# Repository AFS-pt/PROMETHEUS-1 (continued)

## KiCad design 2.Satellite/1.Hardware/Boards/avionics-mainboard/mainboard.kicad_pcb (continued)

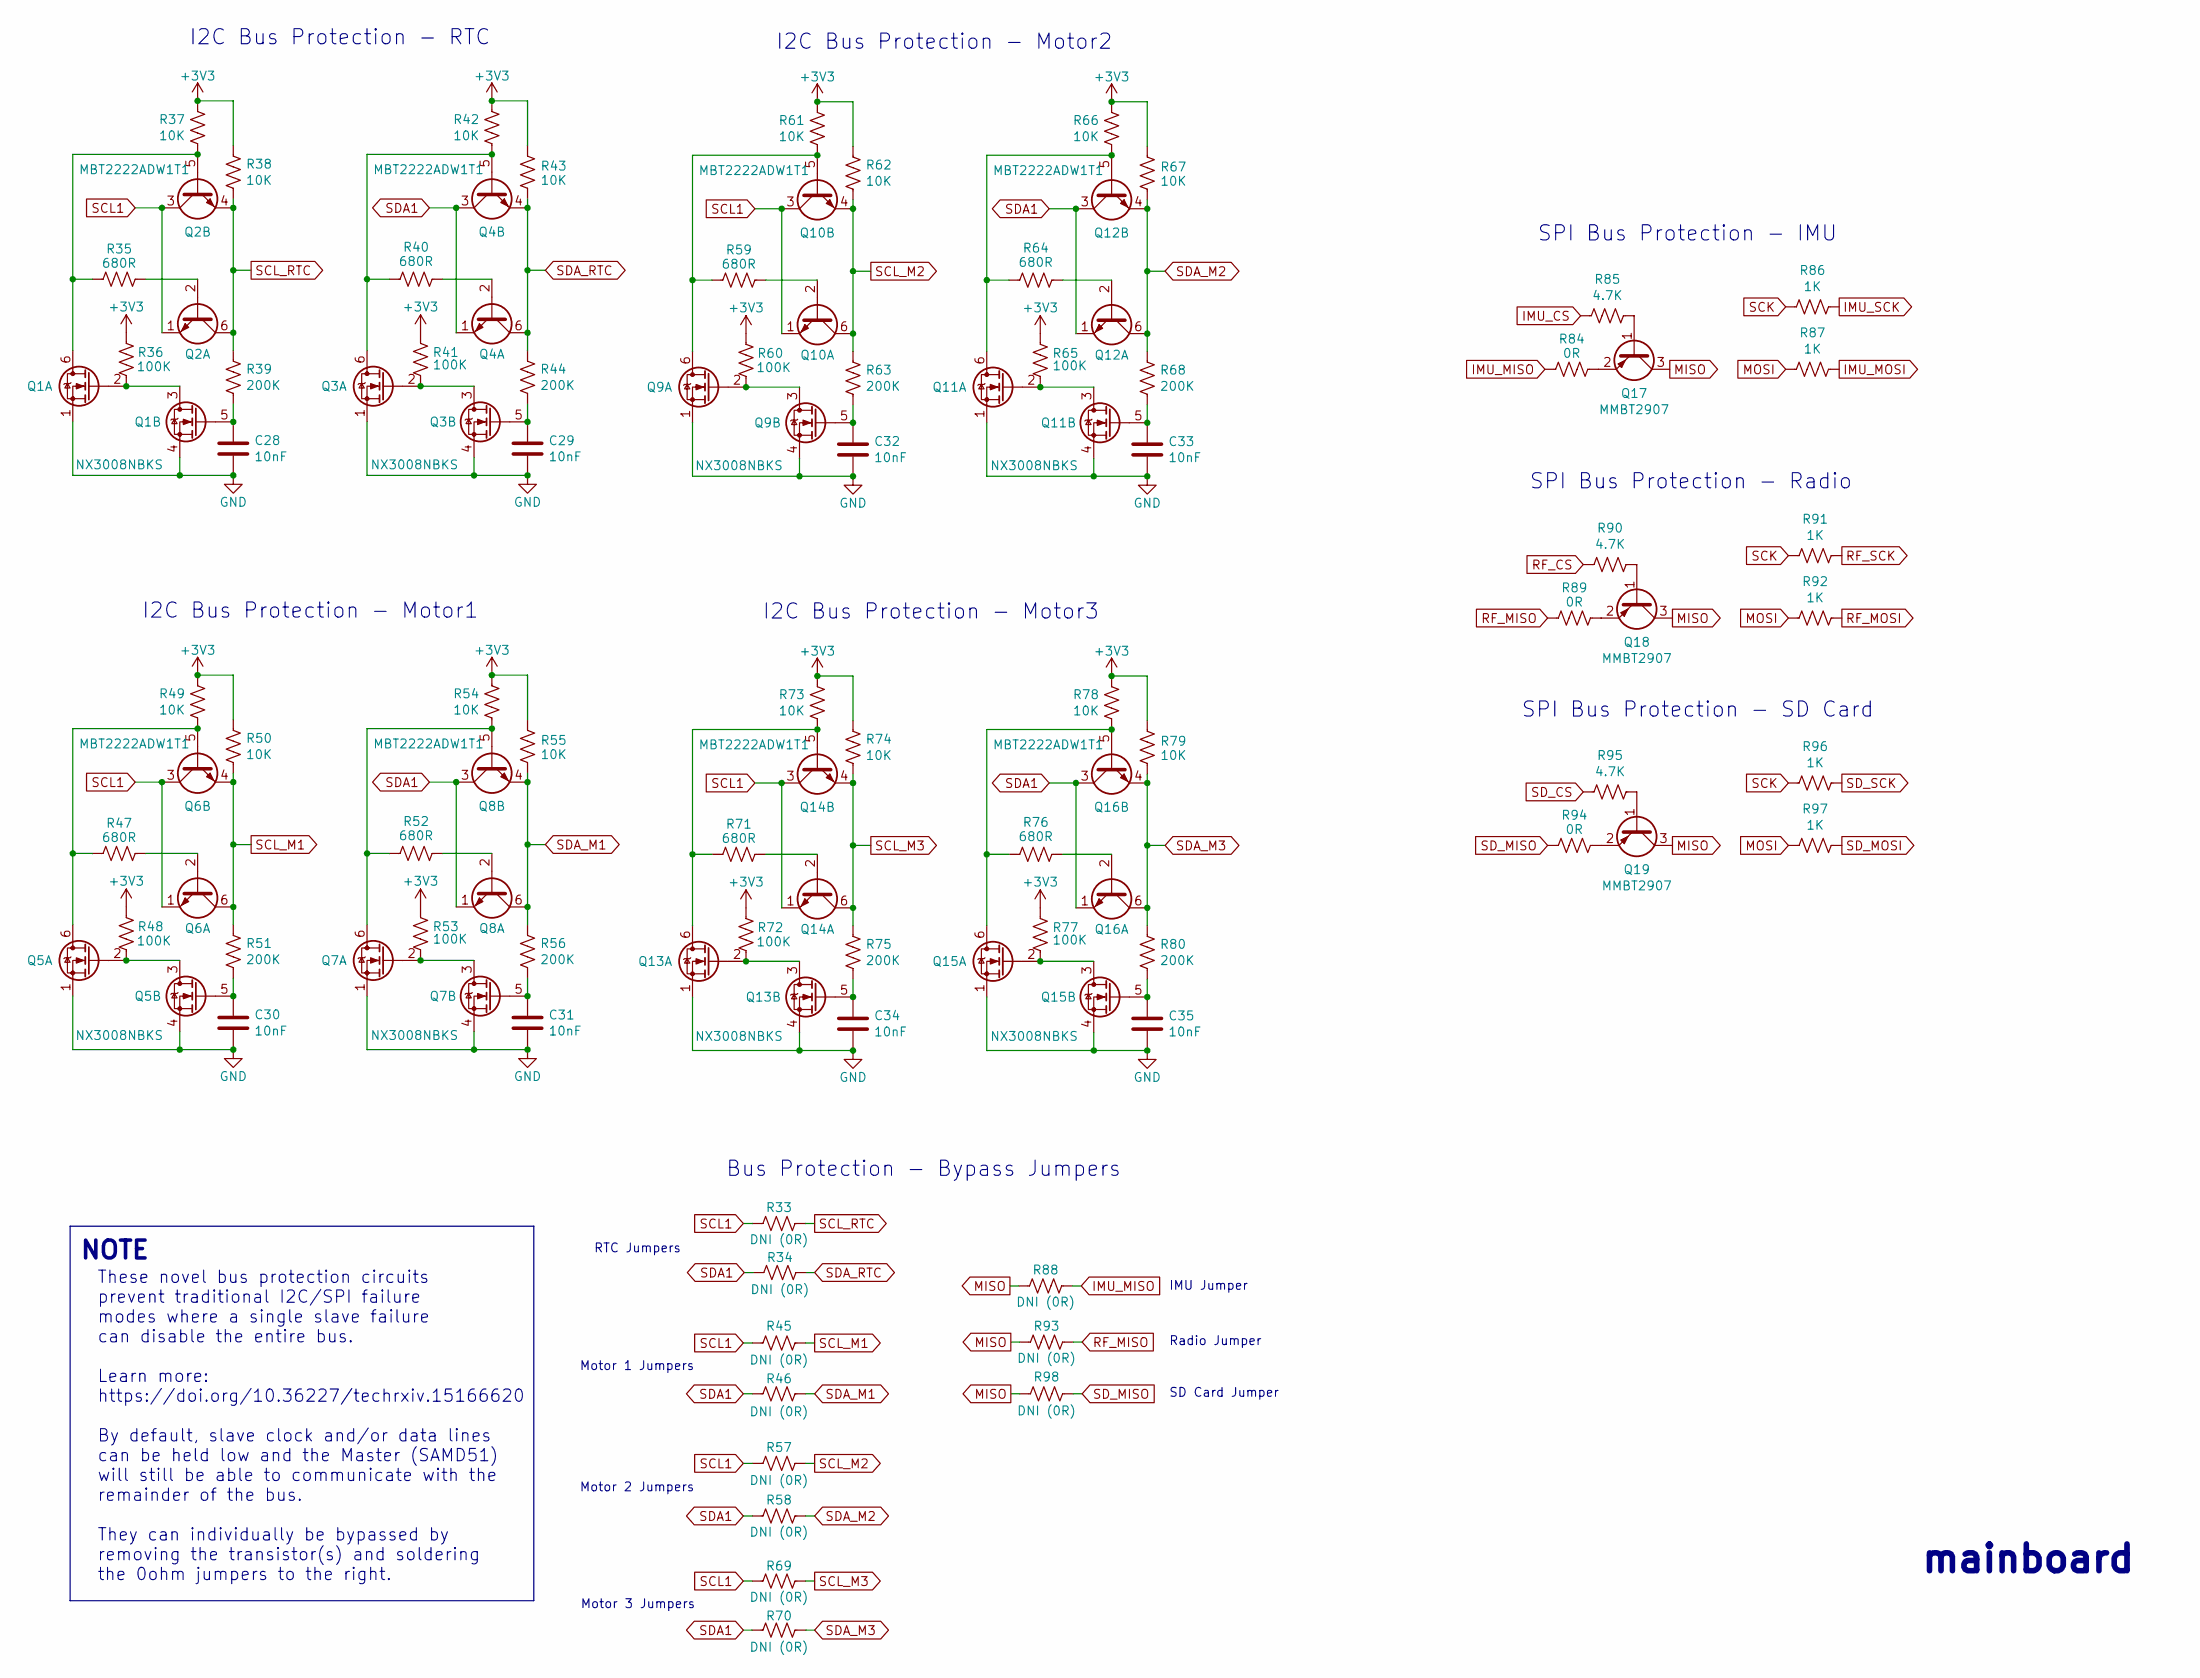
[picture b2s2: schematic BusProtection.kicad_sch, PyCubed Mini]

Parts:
C28, C29, C30, C31, C32, C33, C34, C35: 10nF; C_0603_1608Metric
Q1, Q3, Q5, Q7, Q9, Q11, Q13, Q15: NX3008NBKS; SOT-363_SC-70-6; Manufacturer_Part_Number NX3008NBKS
Q2, Q4, Q6, Q8, Q10, Q12, Q14, Q16: MBT2222ADW1T1; SOT-363_SC-70-6; Manufacturer_Part_Number MBT2222ADW1T1G
Q17, Q18, Q19: MMBT2907; SOT-23; Manufacturer_Part_Number MMBT2907ALT1G
R33, R34, R45, R46, R57, R58, R69, R70, R88, R93, R98: DNI (0R); R_0603_1608Metric
R35, R40, R47, R52, R59, R64, R71, R76: 680R; R_0603_1608Metric
R36, R41, R48, R53, R60, R65, R72, R77: 100K; R_0603_1608Metric
R37, R38, R42, R43, R49, R50, R54, R55, R61, R62, R66, R67, R73, R74, R78, R79: 10K; R_0603_1608Metric
R39, R44, R51, R56, R63, R68, R75, R80: 200K; R_0603_1608Metric
R84, R89, R94: 0R; R_0603_1608Metric
R85, R90, R95: 4.7K; R_0603_1608Metric
R86, R87, R91, R92, R96, R97: 1K; R_0603_1608Metric

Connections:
+3V3: R36.1, R37.1, R38.1, R41.1, R42.1, R43.1, R48.1, R49.1, R50.1, R53.1, R54.1, R55.1, R60.1, R61.1, R62.1, R65.1, R66.1, R67.1, R72.1, R73.1, R74.1, R77.1, R78.1, R79.1; also elsewhere on the board
GND: C28.2, C29.2, C30.2, C31.2, C32.2, C33.2, C34.2, C35.2, Q1.1 (S2), Q1.4 (S1), Q3.1 (S2), Q3.4 (S1), Q5.1 (S2), Q5.4 (S1), Q7.1 (S2), Q7.4 (S1), Q9.1 (S2), Q9.4 (S1), Q11.1 (S2), Q11.4 (S1), Q13.1 (S2), Q13.4 (S1), Q15.1 (S2), Q15.4 (S1); also elsewhere on the board
IMU_CS: R85.2; also elsewhere on the board
IMU_MISO: R84.2, R88.1; also elsewhere on the board
IMU_MOSI: R87.1; also elsewhere on the board
IMU_SCK: R86.1; also elsewhere on the board
MISO: Q17.3 (C), Q18.3 (C), Q19.3 (C), R88.2, R93.2, R98.2; also elsewhere on the board
MOSI: R87.2, R92.2, R97.2; also elsewhere on the board
unnamed: Q1.6 (D1), Q2.5 (B2), R35.2, R37.2
unnamed: Q1.2 (G2), Q1.3 (D2), R36.2
unnamed: C28.1, Q1.5 (G1), R39.2
unnamed: Q2.2 (B1), R35.1
unnamed: Q3.6 (D1), Q4.5 (B2), R40.2, R42.2
unnamed: Q3.2 (G2), Q3.3 (D2), R41.2
unnamed: C29.1, Q3.5 (G1), R44.2
unnamed: Q4.2 (B1), R40.1
unnamed: Q5.6 (D1), Q6.5 (B2), R47.2, R49.2
unnamed: Q5.2 (G2), Q5.3 (D2), R48.2
unnamed: C30.1, Q5.5 (G1), R51.2
unnamed: Q6.2 (B1), R47.1
unnamed: Q7.6 (D1), Q8.5 (B2), R52.2, R54.2
unnamed: Q7.2 (G2), Q7.3 (D2), R53.2
unnamed: C31.1, Q7.5 (G1), R56.2
unnamed: Q8.2 (B1), R52.1
unnamed: Q9.2 (G2), Q9.3 (D2), R60.2
unnamed: C32.1, Q9.5 (G1), R63.2
unnamed: Q10.2 (B1), R59.1
unnamed: Q9.6 (D1), Q10.5 (B2), R59.2, R61.2
unnamed: Q11.6 (D1), Q12.5 (B2), R64.2, R66.2
unnamed: Q11.2 (G2), Q11.3 (D2), R65.2
unnamed: C33.1, Q11.5 (G1), R68.2
unnamed: Q12.2 (B1), R64.1
unnamed: Q13.6 (D1), Q14.5 (B2), R71.2, R73.2
unnamed: Q13.2 (G2), Q13.3 (D2), R72.2
unnamed: C34.1, Q13.5 (G1), R75.2
unnamed: Q14.2 (B1), R71.1
unnamed: Q15.6 (D1), Q16.5 (B2), R76.2, R78.2
unnamed: Q15.2 (G2), Q15.3 (D2), R77.2
unnamed: C35.1, Q15.5 (G1), R80.2
unnamed: Q16.2 (B1), R76.1
unnamed: Q17.1 (B), R85.1
unnamed: Q17.2 (E), R84.1
unnamed: Q18.1 (B), R90.1
unnamed: Q18.2 (E), R89.1
unnamed: Q19.1 (B), R95.1
unnamed: Q19.2 (E), R94.1
RF_CS: R90.2; also elsewhere on the board
RF_MISO: R89.2, R93.1; also elsewhere on the board
RF_MOSI: R92.1; also elsewhere on the board
RF_SCK: R91.1; also elsewhere on the board
SCK: R86.2, R91.2, R96.2; also elsewhere on the board
SCL1: Q2.1 (E1), Q2.3 (C2), Q6.1 (E1), Q6.3 (C2), Q10.1 (E1), Q10.3 (C2), Q14.1 (E1), Q14.3 (C2), R33.2, R45.2, R57.2, R69.2; also elsewhere on the board
SCL_M1: Q6.4 (E2), Q6.6 (C1), R45.1, R50.2, R51.1; also elsewhere on the board
SCL_M2: Q10.4 (E2), Q10.6 (C1), R57.1, R62.2, R63.1; also elsewhere on the board
SCL_M3: Q14.4 (E2), Q14.6 (C1), R69.1, R74.2, R75.1; also elsewhere on the board
SCL_RTC: Q2.4 (E2), Q2.6 (C1), R33.1, R38.2, R39.1; also elsewhere on the board
SDA1: Q4.1 (E1), Q4.3 (C2), Q8.1 (E1), Q8.3 (C2), Q12.1 (E1), Q12.3 (C2), Q16.1 (E1), Q16.3 (C2), R34.2, R46.2, R58.2, R70.2; also elsewhere on the board
SDA_M1: Q8.4 (E2), Q8.6 (C1), R46.1, R55.2, R56.1; also elsewhere on the board
SDA_M2: Q12.4 (E2), Q12.6 (C1), R58.1, R67.2, R68.1; also elsewhere on the board
SDA_M3: Q16.4 (E2), Q16.6 (C1), R70.1, R79.2, R80.1; also elsewhere on the board
SDA_RTC: Q4.4 (E2), Q4.6 (C1), R34.1, R43.2, R44.1; also elsewhere on the board
SD_CS: R95.2; also elsewhere on the board
SD_MISO: R94.2, R98.1; also elsewhere on the board
SD_MOSI: R97.1; also elsewhere on the board
SD_SCK: R96.1; also elsewhere on the board

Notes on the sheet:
SPI Bus Protection - IMU
Motor 3 Jumpers
I2C Bus Protection - RTC
I2C Bus Protection - Motor3
I2C Bus Protection - Motor2
Motor 1 Jumpers
NOTE
SPI Bus Protection - SD Card
Bus Protection - Bypass Jumpers
I2C Bus Protection - Motor1
RTC Jumpers
IMU Jumper
Radio Jumper
mainboard
SPI Bus Protection - Radio
SD Card Jumper
Motor 2 Jumpers
These novel bus protection circuits prevent traditional I2C/SPI failure modes where a single slave failure can disable the entire bus. Learn more: https://doi.org/10.36227/techrxiv.15166620 By default, slave clock and/or data lines can be held low and the Master (SAMD51) will still be able to commu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

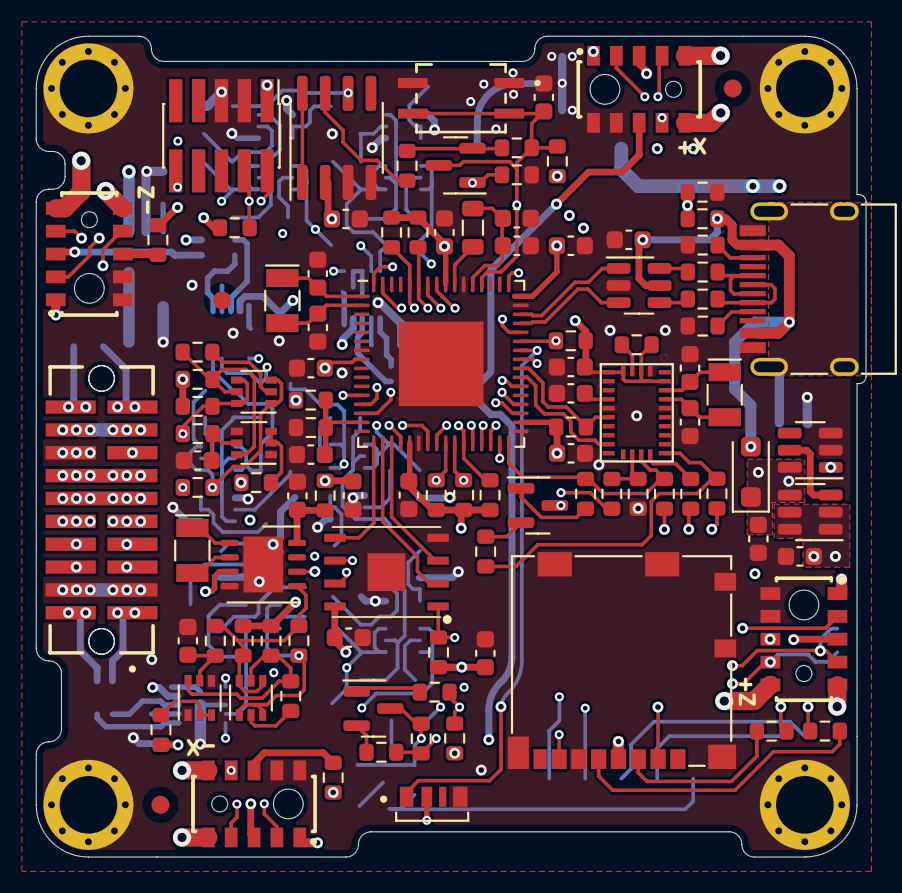
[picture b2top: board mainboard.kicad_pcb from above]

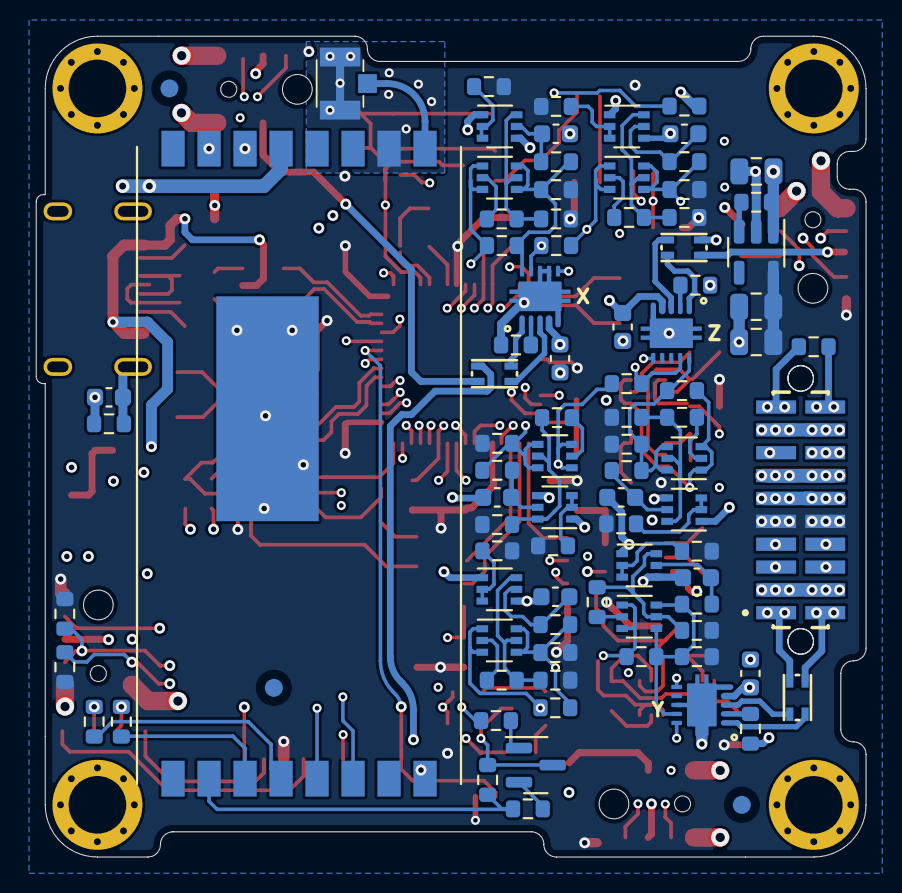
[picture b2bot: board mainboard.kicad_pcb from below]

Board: 4 copper layers, 46.1 x 45.6 mm, 196 parts (86 on the bottom side), 145 nets.

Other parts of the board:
Ref**: Val**; pycubed_mini_half

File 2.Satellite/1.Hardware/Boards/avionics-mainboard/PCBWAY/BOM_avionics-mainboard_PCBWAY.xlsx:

*Designator | *Qty | Manufacturer | *Mfg Part # | Description / Value | *Package/Footprint | Type | Your Instructions / Notes
C28-C35 | 8 | KYOCERA AVX | 06031C103K4T4A | CAP CER 10000PF 100V X7R 0603 | 0603
C26 | 1 | KYOCERA AVX | 06031C472K4T4A | CAP CER 4700PF 100V X7R 0603 | 0603
C1, C2, C3, C4, C5, C10, C13, C19, C21, C23, C24, C25, C27, C36 | 14 | KYOCERA AVX | 06035C104K4T2A | CAP CER 0.1UF 50V X7R 0603 | 0603
C37, C38 | 2 | KYOCERA AVX | 0603YA220J4T2A | CAP CER 22PF 16V C0G/NP0 0603 | 0603 | SMD
C6, C7 | 2 | TDK Corporation | CGA3E2NP01H040C080AA | CAP CER 4PF 50V NP0 0603 | 0603
C8, C17, C18 | 3 | Murata Electronics | GRT188R61C106KE13D | CAP CER 10UF 16V X5R 0603 | 0603
C9, C11, C12, C20, C22 | 5 | Murata Electronics | GRT188R61H105KE13D | CAP CER 1UF 50V X5R 0603 | 0603
C16 | 1 | TDK Corporation | CGA4J1X8R1E105K125AC | CAP CER 1UF 25V X8R 0805 | 0805
C14, C15 | 2 | Murata Electronics | GRT21BC71E106KE13L | CAP CER 10UF 25V X7S 0805 | 0805
J1 | 1 | Amphenol ICC (FCI) | 20021121-00010C4LF | CONN HEADER SMD 10POS 1.27MM |  | SMD
J4 | 1 | GCT | USB4105-GF-A | CONN RCP USB2.0 TYP C 24P SMD RA |  | SMD
Y3 | 1 | Micro Crystal | CC7V-T1A-32.768k-12.5pF-20PPM-TC-QA | Crystals 32.768 kHz 12.5 pF +/-20 PPM AEC-Q200 |  | SMD
Y1, Y2 | 2 | Micro Crystal | CC7V-T1A-32.768k-7pF-20PPM-TB-QA | Crystals 32.768 kHz 7.0 pF +/-20 PPM AEC-Q200 |  | SMD
D2 | 1 | Panjit International Inc. | MBR1020VL-AU_R1_000A1 | DIODE SCHOTTKY 20V 1A SOD123FL | SOD-123F
L1 | 1 | Coilcraft | 0805LS-103XGRC | RF INDUCTOR, FERRITE CORE, 2% TO | 0805
U12 | 1 | CEVA Technologies, Inc. | BNO085 | IMU ACCEL/GYRO/MAG I2C 32BIT | 28-LGA
J3 | 1 | Molex | 1040310811 | CONN MICRO SD CARD PUSH-PULL R/A |  | SMD
U4 | 1 | Everspin Technologies Inc. | MR25H40DF | IC RAM 4MBIT SPI 40MHZ 8DFN | 8-DFN-EP
U6 | 1 | HOPE MICROELECTRONICS | RFM98PW-433S2 | Module: transceiver; RF; FSK,GFSK,GMSK,LoRa,MSK,OOK; 433.92MHz |  | SMD
J7, J8, J9, J10 | 4 | Samtec Inc. | CLP-105-02-F-DH-A | CONN RCPT 10P 0.05 GOLD SMD R/A |  | SMD
J5 | 1 | Samtec Inc. | SFC-110-T2-F-D-A | CONN RCPT 20POS 0.05 GOLD SMD |  | SMD
J6 | 1 | Samtec Inc. | TFM-110-12-L-D-A | CONN HEADER SMD 20POS 1.27MM |  | SMD
D1 | 1 | Adafruit Industries LLC | 4691 | ADDRESS LED DISCRETE RGB 4X2MM |  | SMD
SW1 | 1 | Würth Elektronik | 434331045822 | SWITCH TACTILE SPST-NO 0.05A 12V |  | SMD
FL1, FL2, FL3 | 3 | Bourns Inc. | SRF2012A-670YA | CMC 400MA 2LN 67OHM SMD AEC-Q200 | 0805 | SMD
J2 | 1 | Hirose Electric Co Ltd | U.FL-R-SMT-1(80) | CONN U.FL RCPT STR 50 OHM SMD |  | SMD
U7-U9 | 3 | Texas Instruments | DRV8830DRCT | IC MTRDRV BIPLR 2.75-6.8V 10VSON | 10-VSON
U1 | 1 | Microchip Technology | ATSAMD51J19A-M | IC MCU 32BIT 512KB FLASH 64QFN | 64-QFN
U2 | 1 | Analog Devices Inc./Maxim Integrated | MAX706RESA+T | IC SUPERVISOR 1 CHANNEL 8SOIC | 8-SOIC
U11 | 1 | NXP USA Inc. | PCF8523TK/1,118 | IC RTC CLK/CALENDAR I2C 8HVSON | 8-HVSON
Q21 | 1 | Infineon Technologies | IRLML2803TRPBF | MOSFET N-CH 30V 1.2A SOT23 | SOT-23-3
Q17-Q19 | 3 | Diodes Incorporated | MMBT2907A-7-F | TRANS PNP 60V 0.6A SOT23-3 | SOT-23-3
U3 | 1 | Diodes Incorporated | AP2112K-3.3TRG1 | IC REG LINEAR 3.3V 600MA SOT25 | SOT-25
Q20 | 1 | Vishay Siliconix | SQ3495EV-T1_GE3 | MOSFET P-CH 30V 8A 6TSOP | SOT-23-6 | SMD
U10 | 1 | STMicroelectronics | USBLC6-2SC6 | TVS DIODE 5.25VWM 17VC SOT23-6 | SOT-23-6
Q2, Q4, Q6, Q8, Q10, Q12, Q14, Q16 | 8 | onsemi | MBT2222ADW1T1G | TRANS 2NPN 40V 0.6A SC88/SC70-6 | SOT-363
Q1, Q3, Q5, Q7, Q9, Q11, Q13, Q15 | 8 | Nexperia USA Inc. | NX3008NBKS,115 | MOSFET 2N-CH 30V 0.35A 6TSSOP | 6-TSSOP
U5 | 1 | Analog Devices Inc. | LTC4412ES6#TRMPBF | IC OR CTRLR SRC SELECT TSOT23-6 | TSOT-23-6
R39, R44, R51, R56, R63, R68, R75, R80, R100 | 9 | Stackpole Electronics Inc | RMCF0603FT200K | RES 200K OHM 1% 1/10W 0603 | 0603
R28, R29 | 2 | Stackpole Electronics Inc | RMCF0603FT22R0 | RES 22 OHM 1% 1/10W 0603 | 0603
R35, R40, R47, R52, R59, R64, R71, R76 | 8 | Stackpole Electronics Inc | RMCF0603FT680R | RES 680 OHM 1% 1/10W 0603 | 0603
R13, R20-R22, R26, R30-R32, R84, R89, R94 | 11 | Stackpole Electronics Inc | RMCF0603ZT0R00 | RES 0 OHM JUMPER 1/10W 0603 | 0603
R23 | 1 | Stackpole Electronics Inc | RNCF0603BKC1M00 | RES 1M OHM 0.1% 1/10W 0603 | 0603
R3-R10, R14, R16-R19, R37, R38, R42, R43, R49, R50, R54, R55, R61, R62, R66, R6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 | 32 | Stackpole Electronics Inc | RNCF0603BTE10K0 | RES 10K OHM 0.1% 1/6W 0603 | 0603
R1, R2, R11, R27, R36, R41, R48, R53, R60, R65, R72, R77 | 12 | Stackpole Electronics Inc | RNCF0603DTE100K | RES 100K OHM 0.5% 1/6W 0603 | 0603
R12, R15, R86, R87, R91, R92, R96, R97 | 8 | Stackpole Electronics Inc | RNCF0603DTE1K00 | RES 1K OHM 0.5% 1/6W 0603 | 0603
R85, R90, R95 | 3 | Stackpole Electronics Inc | RNCF0603DTE4K70 | RES 4.7K OHM 0.5% 1/6W 0603 | 0603
R24, R25 | 2 | Stackpole Electronics Inc | RNCF0603DTE5K10 | RES 5.1K OHM 0.5% 1/6W 0603 | 0603

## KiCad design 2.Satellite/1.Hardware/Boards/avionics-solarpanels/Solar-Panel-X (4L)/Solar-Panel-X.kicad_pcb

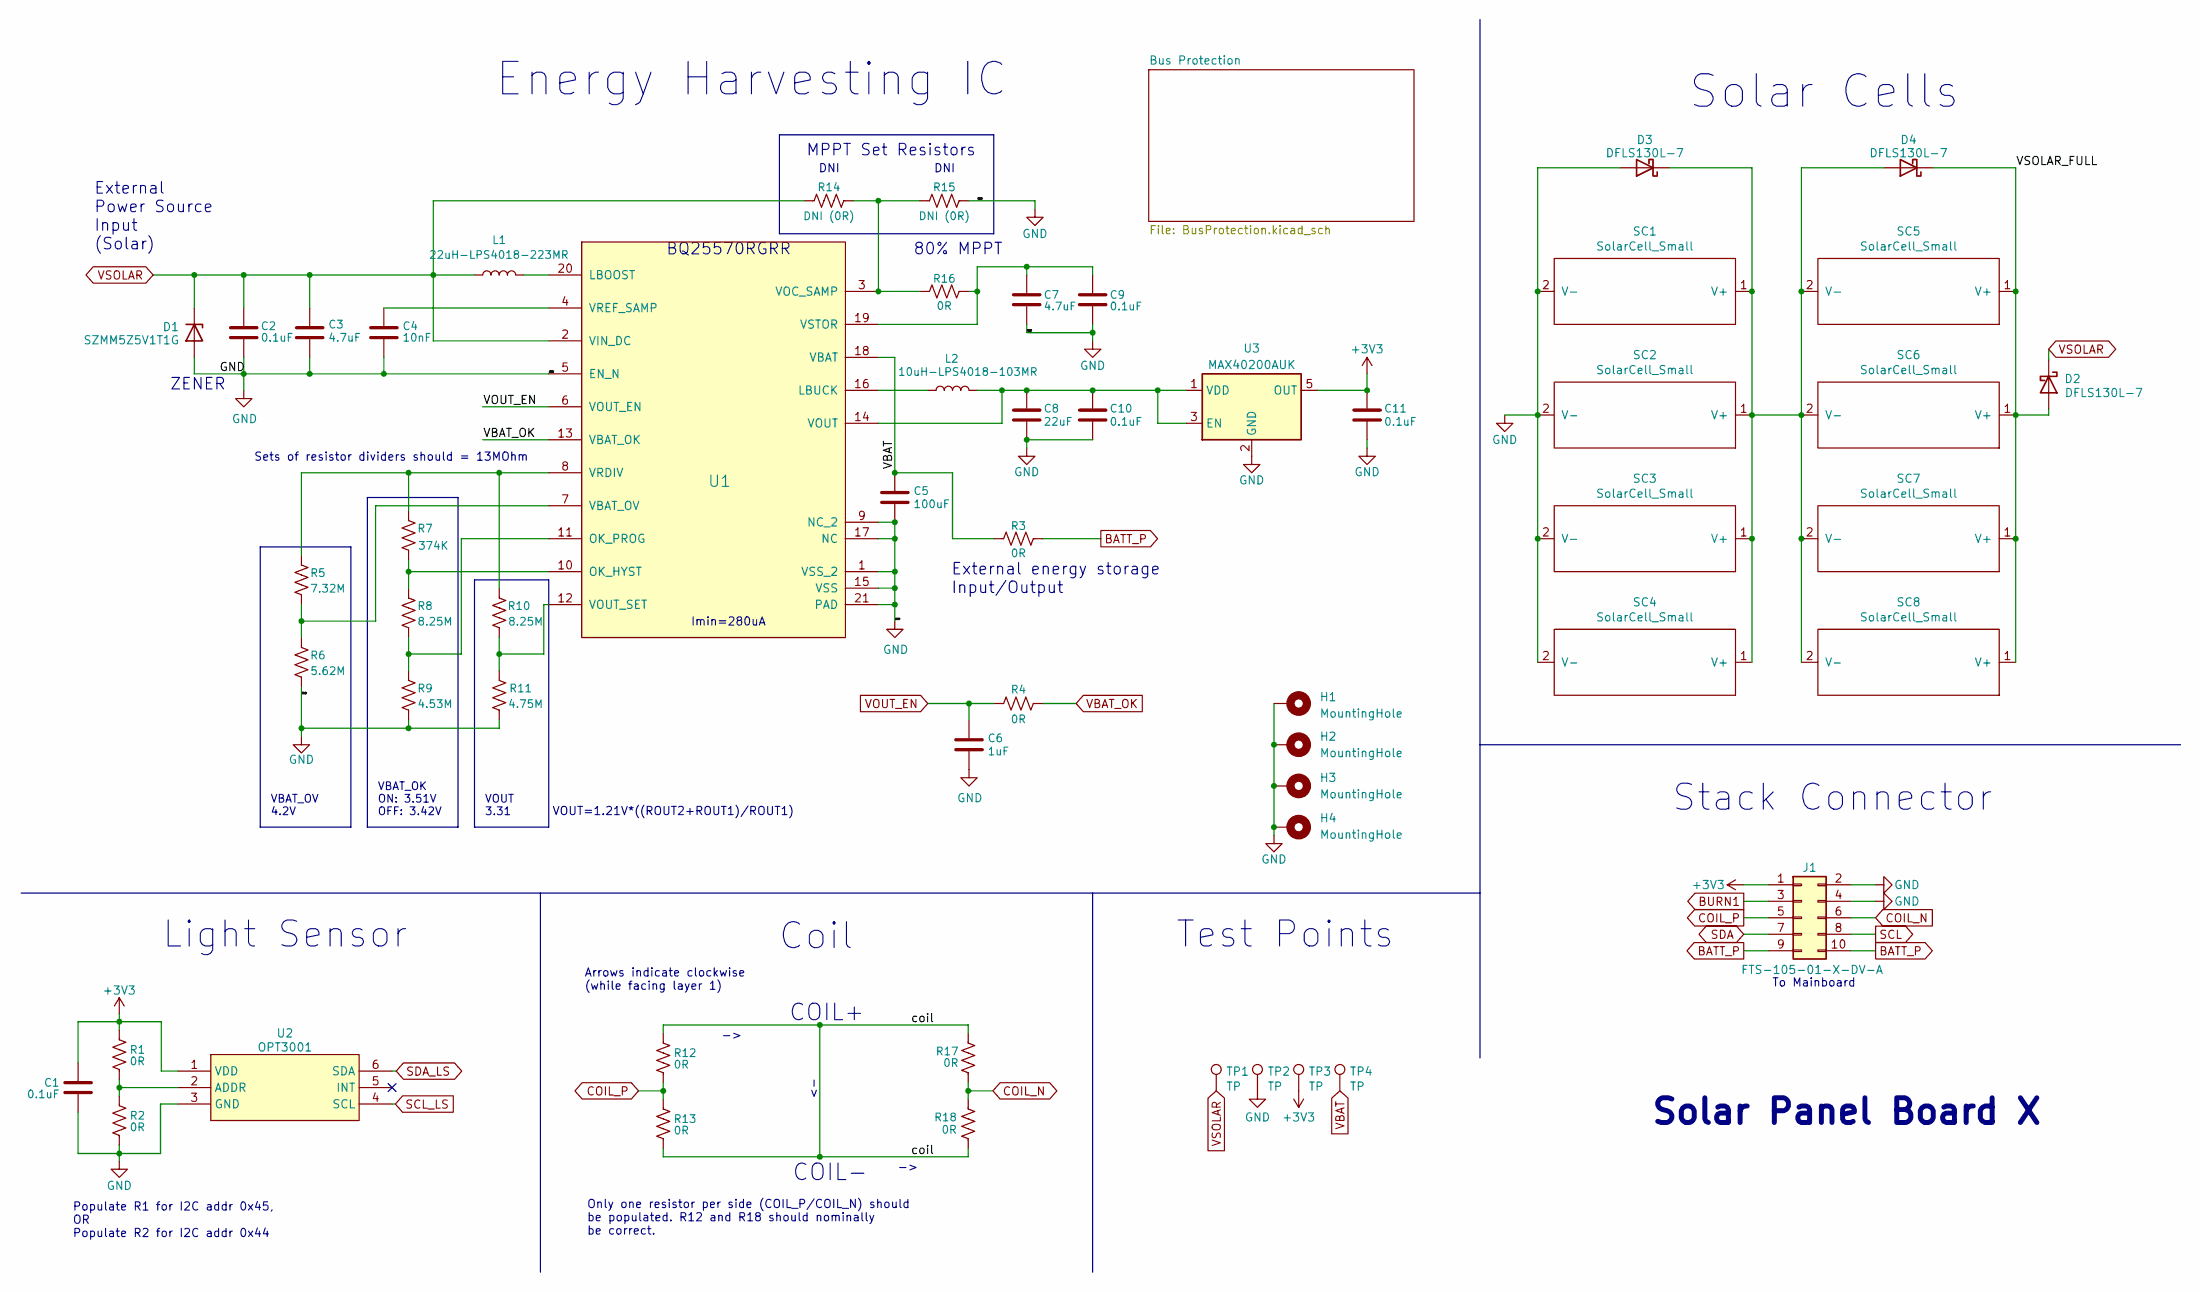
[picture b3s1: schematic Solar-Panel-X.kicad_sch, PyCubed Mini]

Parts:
C1: 0.1uF; C_0402_1005Metric
C2, C9, C10, C11: 0.1uF; C_0603_1608Metric
C3, C7: 4.7uF; C_0603_1608Metric
C4: 10nF; C_0603_1608Metric
C5: 100uF; C_0805_2012Metric
C6: 1uF; C_0603_1608Metric
C8: 22uF; C_0603_1608Metric
D1: SZMM5Z5V1T1G; D_SOD-523
D2, D3, D4: DFLS130L-7; D_PowerDI-123
H1, H2, H3, H4: MountingHole; MountingHole_2.2mm_M2_DIN965_Pad_TopBottom
J1: FTS-105-01-X-DV-A; SAMTEC-FTS-105-01-X-DV-A
L1: 22uH-LPS4018-223MR; LPS4018
L2: 10uH-LPS4018-103MR; LPS4018
R1, R2: 0R; R_0402_1005Metric
R3, R4, R12, R13, R16, R17, R18: 0R; R_0603_1608Metric
R5: 7.32M; R_0603_1608Metric
R6: 5.62M; R_0603_1608Metric
R7: 374K; R_0603_1608Metric
R8, R10: 8.25M; R_0603_1608Metric
R9: 4.53M; R_0603_1608Metric
R11: 4.75M; R_0603_1608Metric
R14, R15: DNI (0R); R_0603_1608Metric
SC1, SC2, SC3, SC4, SC5, SC6, SC7, SC8: SolarCell_Small; KXOB25-05X3F
TP1, TP2, TP3, TP4: TP; TestPoint_THTPad_D1.0mm_Drill0.5mm
U1: BQ25570RGRR; QFN50P350X350X100-21N-D
U2: OPT3001
U3: MAX40200AUK; SOT-23-5

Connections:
+3V3: C1.2, C11.1, J1.1, R1.2, TP3.1, U2.1 (VDD), U3.5 (OUT); also elsewhere on the board
/VSOLAR_FULL: D2.2 (A), D4.1 (K), SC5.1 (V+), SC6.1 (V+), SC7.1 (V+), SC8.1 (V+)
/coil: R12.2, R13.1, R17.2, R18.1
BATT_P: J1.9, J1.10, R3.1
BURN1: J1.3
COIL_N: J1.6, R17.1, R18.2
COIL_P: J1.5, R12.1, R13.2
GND: C1.1, C2.2, C3.2, C4.2, C5.2, C6.2, C7.2, C8.2, C9.2, C10.2, C11.2, D1.2 (A), D3.2 (A), H1.1, H2.1, H3.1, H4.1, J1.2, J1.4, R2.1, R6.1, R9.1, R11.1, R15.1, SC1.2 (V-), SC2.2 (V-), SC3.2 (V-), SC4.2 (V-), TP2.1, U1.1 (VSS_2), U1.5 (EN_N), U1.9 (NC_2), U1.15 (VSS), U1.17 (NC), U1.21 (PAD), U2.3 (GND), U2.7 (GND), U3.2 (GND); also elsewhere on the board
unnamed: D3.1 (K), D4.2 (A), SC1.1 (V+), SC2.1 (V+), SC3.1 (V+), SC4.1 (V+), SC5.2 (V-), SC6.2 (V-), SC7.2 (V-), SC8.2 (V-)
unnamed: L1.2, U1.20 (LBOOST)
unnamed: L2.1, U1.16 (LBUCK)
unnamed: R7.1, R8.2, U1.10 (OK_HYST)
unnamed: R8.1, R9.2, U1.11 (OK_PROG)
unnamed: R5.1, R6.2, U1.7 (VBAT_OV)
unnamed: R14.1, R15.2, R16.2, U1.3 (VOC_SAMP)
unnamed: C8.1, C10.1, L2.2, U1.14 (VOUT), U3.1 (VDD), U3.3 (EN)
unnamed: R10.1, R11.2, U1.12 (VOUT_SET)
unnamed: R5.2, R7.2, R10.2, U1.8 (VRDIV)
unnamed: C4.1, U1.4 (VREF_SAMP)
unnamed: C7.1, C9.1, R16.1, U1.19 (VSTOR)
unnamed: R1.1, R2.2, U2.2 (ADDR)
SCL: J1.8; also elsewhere on the board
SCL_LS: U2.4 (SCL); also elsewhere on the board
SDA: J1.7; also elsewhere on the board
SDA_LS: U2.6 (SDA); also elsewhere on the board
VBAT: C5.1, R3.2, TP4.1, U1.18 (VBAT)
VBAT_OK: R4.1, U1.13 (VBAT_OK)
VOUT_EN: C6.1, R4.2, U1.6 (VOUT_EN)
VSOLAR: C2.1, C3.1, D1.1 (K), D2.1 (K), L1.1, R14.2, TP1.1, U1.2 (VIN_DC)

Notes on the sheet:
80% MPPT
DNI
Populate R1 for I2C addr 0x45, OR Populate R2 for I2C addr 0x44
Solar Cells
External Power Source Input (Solar)
Only one resistor per side (COIL_P/COIL_N) should be populated. R12 and R18 should nominally be correct.
Stack Connector
VOUT 3.31
Energy Harvesting IC
MPPT Set Resistors
Arrows indicate clockwise (while facing layer 1)
Test Points
External energy storage Input/Output
COIL+
BQ25570RGRR
Light Sensor
Solar Panel Board X
VOUT=1.21V*((ROUT2+ROUT1)/ROUT1)
VBAT_OV 4.2V
VBAT_OK ON: 3.51V OFF: 3.42V
COIL-
Sets of resistor dividers should = 13MOhm
Imin=280uA
ZENER
To Mainboard
Coil

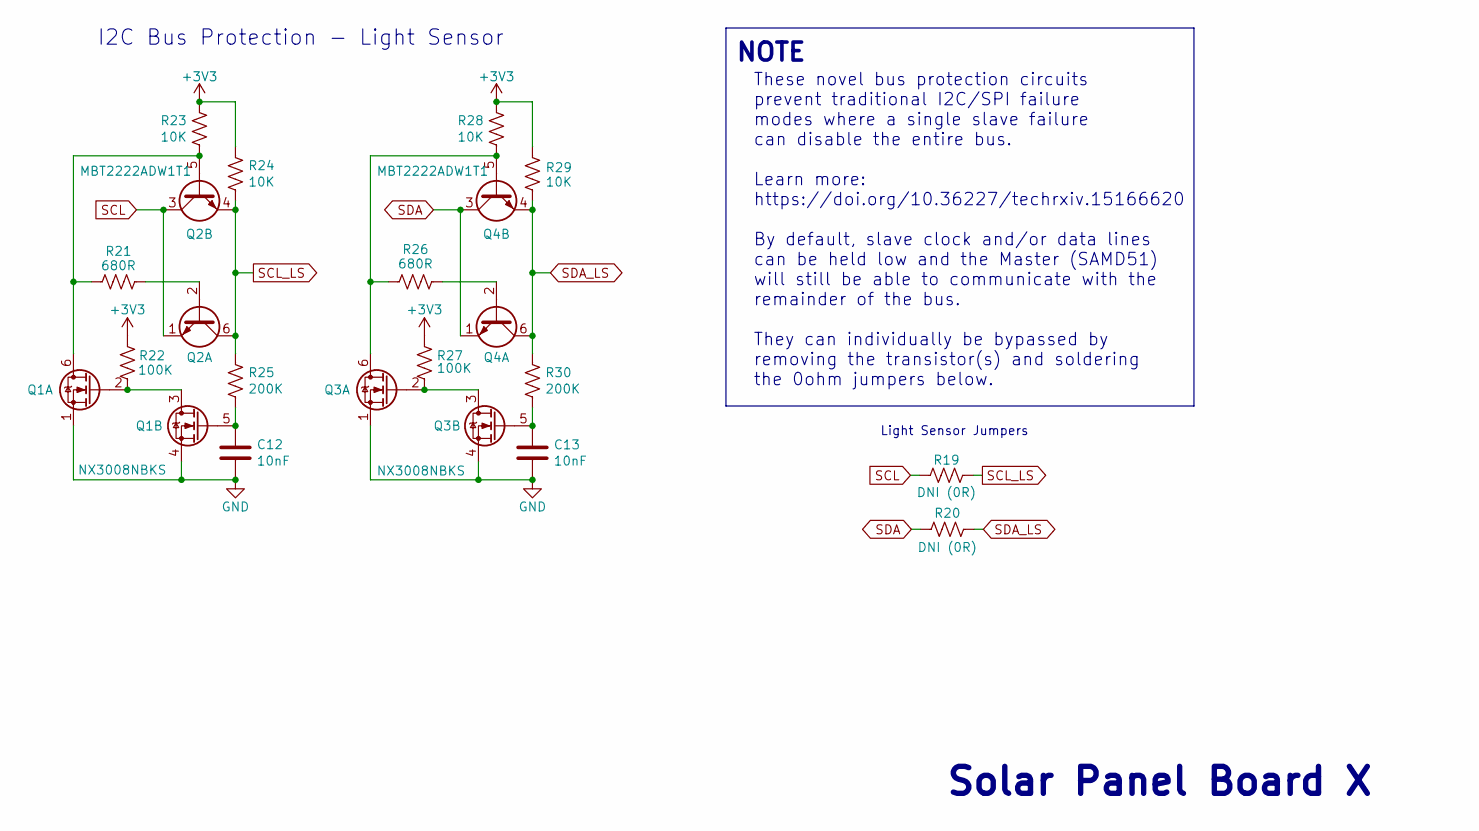
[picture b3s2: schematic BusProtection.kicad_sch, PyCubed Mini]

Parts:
C12, C13: 10nF; C_0603_1608Metric
Q1, Q3: NX3008NBKS; SOT-363_SC-70-6; Manufacturer_Part_Number NX3008NBKS
Q2, Q4: MBT2222ADW1T1; SOT-363_SC-70-6; Manufacturer_Part_Number MBT2222ADW1T1G
R19, R20: DNI (0R); R_0603_1608Metric
R21, R26: 680R; R_0603_1608Metric
R22, R27: 100K; R_0603_1608Metric
R23, R24, R28, R29: 10K; R_0603_1608Metric
R25, R30: 200K; R_0603_1608Metric

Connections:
+3V3: R22.1, R23.1, R24.1, R27.1, R28.1, R29.1; also elsewhere on the board
GND: C12.2, C13.2, Q1.1 (S2), Q1.4 (S1), Q3.1 (S2), Q3.4 (S1); also elsewhere on the board
unnamed: Q1.6 (D1), Q2.5 (B2), R21.2, R23.2
unnamed: Q1.2 (G2), Q1.3 (D2), R22.2
unnamed: C12.1, Q1.5 (G1), R25.2
unnamed: Q2.2 (B1), R21.1
unnamed: Q3.6 (D1), Q4.5 (B2), R26.2, R28.2
unnamed: Q3.2 (G2), Q3.3 (D2), R27.2
unnamed: C13.1, Q3.5 (G1), R30.2
unnamed: Q4.2 (B1), R26.1
SCL: Q2.1 (E1), Q2.3 (C2), R19.2; also elsewhere on the board
SCL_LS: Q2.4 (E2), Q2.6 (C1), R19.1, R24.2, R25.1; also elsewhere on the board
SDA: Q4.1 (E1), Q4.3 (C2), R20.2; also elsewhere on the board
SDA_LS: Q4.4 (E2), Q4.6 (C1), R20.1, R29.2, R30.1; also elsewhere on the board

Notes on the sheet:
Solar Panel Board X
These novel bus protection circuits prevent traditional I2C/SPI failure modes where a single slave failure can disable the entire bus. Learn more: https://doi.org/10.36227/techrxiv.15166620 By default, slave clock and/or data lines can be held low and the Master (SAMD51) will still be able to commu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
NOTE
I2C Bus Protection - Light Sensor
Light Sensor Jumpers

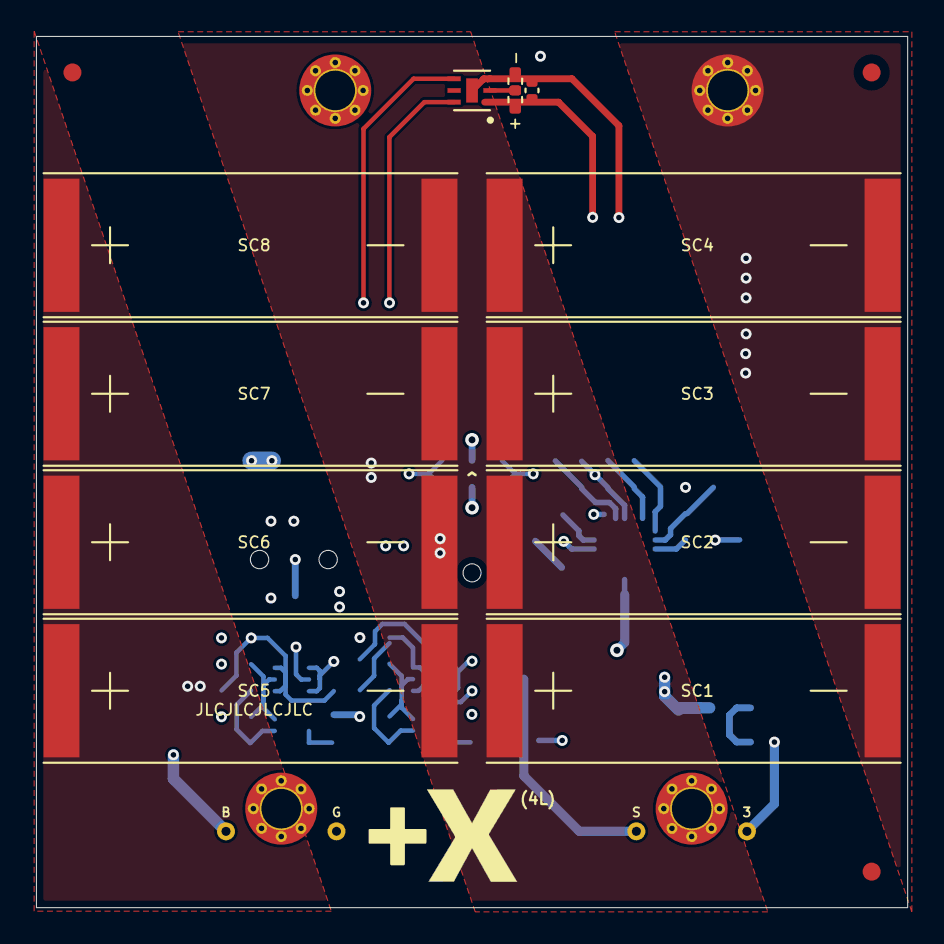
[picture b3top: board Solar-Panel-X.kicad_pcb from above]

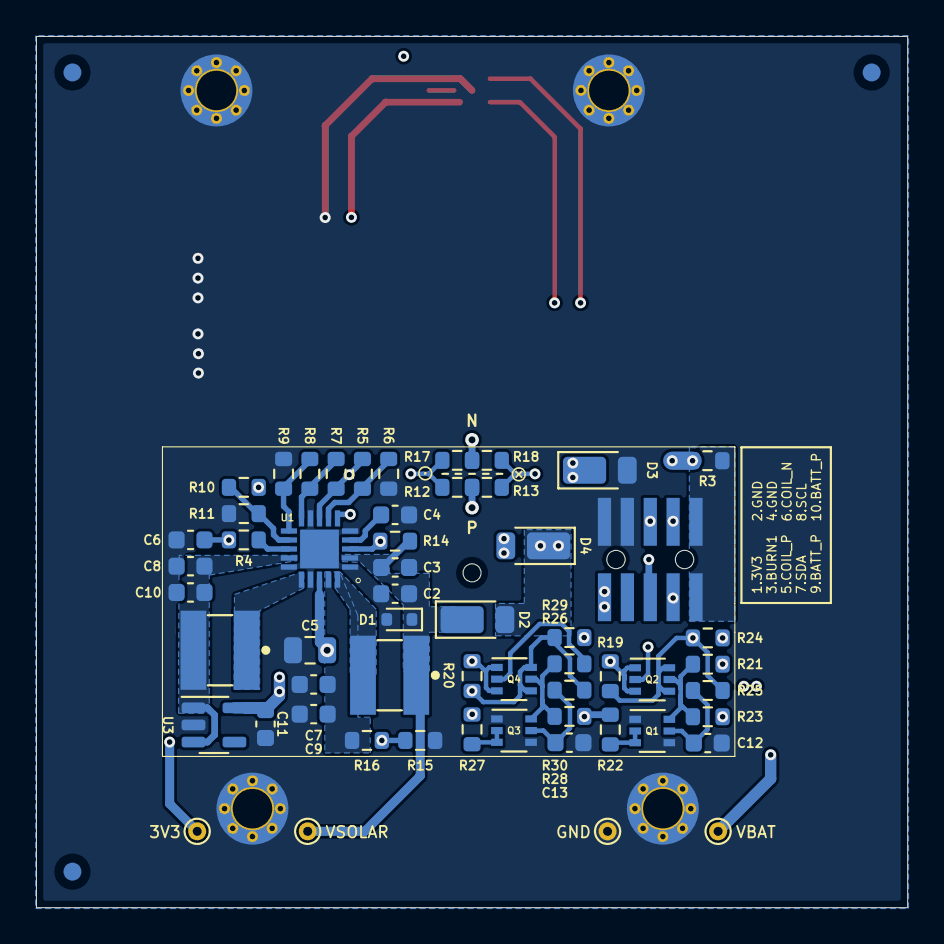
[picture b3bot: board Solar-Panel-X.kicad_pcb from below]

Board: 4 copper layers, 48.4 x 48.4 mm, 74 parts (58 on the bottom side), 36 nets.

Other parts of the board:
Ref**: Val**; pycubed_mini_half

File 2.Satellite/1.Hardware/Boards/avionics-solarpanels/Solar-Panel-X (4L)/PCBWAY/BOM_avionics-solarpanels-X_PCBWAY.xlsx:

*Designator | *Qty | Manufacturer | *Mfg Part # | Description / Value | *Package/Footprint | Type | Your Instructions / Notes
C1 | 1 | KYOCERA AVX | 04025C104KAT2A | CAP CER 0.1UF 50V X7R 0402 | 0402
C4, C12, C13 | 3 | KYOCERA AVX | 06031C103K4T4A | CAP CER 10000PF 100V X7R 0603 | 0603
C2, C9-C11 | 4 | KYOCERA AVX | 06035C104K4T2A | CAP CER 0.1UF 50V X7R 0603 | 0603
C8 | 1 | Murata Electronics | GRT188R61A226ME13D | CAP CER 22UF 10V X5R 0603 | 0603
C6 | 1 | Murata Electronics | GRT188R61H105KE13D | CAP CER 1UF 50V X5R 0603 | 0603
C3, C7 | 2 | Murata Electronics | GRT188R6YA475KE13D | CAP CER 4.7UF 35V X5R 0603 | 0603
C5 | 1 | Murata Electronics | GRM21BR60J107ME15K | CAP CER 100UF 6.3V X5R 0805 | 0805
D2-D4 | 3 | Diodes Incorporated | DFLS130L-7 | DIODE SCHOTTKY 30V 1A PWRDI123 | PowerDI-123
D1 | 1 | onsemi | SZMM5Z5V1T1G | DIODE ZENER 5.1V 500MW SOD523 | SOD-523
U3 | 1 | Analog Devices Inc./Maxim Integrated | MAX40200AUK+T | MAX40200AUK+T | SOT-23-5
Q2, Q4 | 2 | onsemi | MBT2222ADW1T1G | TRANS 2NPN 40V 0.6A SC88/SC70-6 | SOT-363
Q1, Q3 | 2 | Nexperia USA Inc. | NX3008NBKS,115 | MOSFET 2N-CH 30V 0.35A 6TSSOP | 6-TSSOP
R1, R2 | 2 | Stackpole Electronics Inc | RMCF0402ZT0R00 | RES 0 OHM JUMPER 1/16W 0402 | 0402
R8, R10 | 2 | Vishay Dale | CRCW06038M25FKEA | RES SMD 8.25M OHM 1% 1/10W 0603 | 0603
R25, R30 | 2 | Stackpole Electronics Inc | RMCF0603FT200K | RES 200K OHM 1% 1/10W 0603 | 0603
R7 | 1 | Stackpole Electronics Inc | RMCF0603FT374K | RES 374K OHM 1% 1/10W 0603 | 0603
R9 | 1 | Stackpole Electronics Inc | RMCF0603FT4M53 | RES 4.53M OHM 1% 1/10W 0603 | 0603
R11 | 1 | Stackpole Electronics Inc | RMCF0603FT4M75 | RES 4.75M OHM 1% 1/10W 0603 | 0603
R6 | 1 | Stackpole Electronics Inc | RMCF0603FT5M62 | RES 5.62M OHM 1% 1/10W 0603 | 0603
R21, R26 | 2 | Stackpole Electronics Inc | RMCF0603FT680R | RES 680 OHM 1% 1/10W 0603 | 0603
R5 | 1 | Stackpole Electronics Inc | RMCF0603FT7M32 | RES 7.32M OHM 1% 1/10W 0603 | 0603
R3, R4, R12, R13, R16-R18 | 7 | Stackpole Electronics Inc | RMCF0603ZT0R00 | RES 0 OHM JUMPER 1/10W 0603 | 0603
R23, R24, R28, R29 | 4 | Stackpole Electronics Inc | RNCF0603BTE10K0 | RES 10K OHM 0.1% 1/6W 0603 | 0603
R22, R27 | 2 | Stackpole Electronics Inc | RNCF0603DTE100K | RES 100K OHM 0.5% 1/6W 0603 | 0603
SC1-SC8 | 8 | ANYSOLAR Ltd | KXOB25-05X3F-TR | MONOCRYS SOLAR CELL 30.7MW 2.07V |  | SMD
L2 | 1 | Coilcraft | LPS4018-103MRC | Power Inductors - SMD 10uH Shld 20% 1.3A 200 mOhms | 1515 | SMD
L1 | 1 | Coilcraft | LPS4018-223MRC | Power Inductors - SMD 22uH Shld 20% 830mA 360 mOhms | 1515 | SMD
U2 | 1 | Texas Instruments | OPT3001IDNPRQ1 | SENSOR OPT 550NM AMBIENT 6USON | 6-USON
U1 | 1 | Texas Instruments | BQ25570RGRR | IC ENERGY HARV CTRLR BATT 20VQFN | 20-VQFN
J1 | 1 | Samtec Inc. | FTS-105-01-L-DV-A-P-TR | CONN HEADER SMD 10POS 1.27MM |  | SMD

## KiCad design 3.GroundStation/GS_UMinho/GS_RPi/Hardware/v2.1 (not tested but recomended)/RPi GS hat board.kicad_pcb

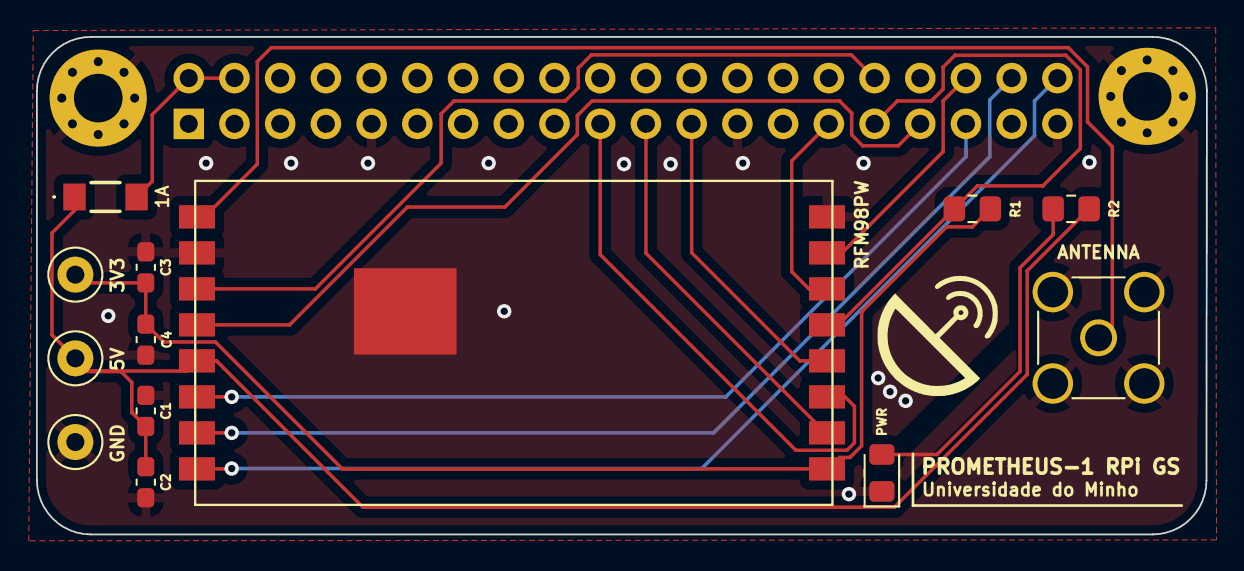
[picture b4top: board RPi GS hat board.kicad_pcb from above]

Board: 2 copper layers, 65.0 x 27.6 mm, 16 parts (1 on the bottom side), 17 nets.

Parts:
1A: 1A; ERBRG4R00V
3V3: 3.3V; TestPoint_Loop_D2.50mm_Drill1.0mm
5V: 5V; TestPoint_Loop_D2.50mm_Drill1.0mm
ANTENNA: Coax SMA; SMA_Amphenol_901-144_Vertical
C1, C3: 10uF; C_0603_1608Metric_Pad1.08x0.95mm_HandSolder
C2, C4: 0.1uF; C_0603_1608Metric_Pad1.08x0.95mm_HandSolder
GND: GND; TestPoint_Loop_D2.50mm_Drill1.0mm
H1, H2: M; MountingHole_2.7mm_M2.5_Pad_Via
J4: Raspberry_Pi_2_3; PinSocket_2x20_P2.54mm_Vertical
PWR: POW; LED_0805_2012Metric_Pad1.15x1.40mm_HandSolder
R1: 10K; R_0805_2012Metric_Pad1.20x1.40mm_HandSolder
R2: 200; R_0805_2012Metric_Pad1.20x1.40mm_HandSolder
U1: RFM98PW; RFM95PW

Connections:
+3V3: 3V3.1, C3.1, C4.1, R1.2, U1.9 (3.3V)
/5V: 1A.1, 5V.1, C1.1, C2.1, R2.2, U1.5 (VCC)
/RF_ANT: ANTENNA.1 (In), U1.1 (ANT)
/RF_CS: J4.31 (GCLK2/GPIO6), R1.1, U1.13 (NSS)
/RF_DIO0: J4.35 (GPIO19/MISO1), U1.6 (GPIO_0)
/RF_DIO1: J4.38 (GPIO20/MOSI1), U1.7 (GPIO_1)
/RF_DIO2: J4.40 (GPIO21/SCLK1), U1.8 (GPIO_2)
/RF_DIO3: J4.32 (PWM0/GPIO12), U1.3 (GPIO_3)
/RF_DIO4: J4.33 (PWM1/GPIO13), U1.4 (GPIO_4)
/RF_DIO5: J4.36 (GPIO16), U1.15 (GPIO_5)
/RF_MISO: J4.21 (MISO0/GPIO9), U1.10 (MISO)
/RF_MOSI: J4.19 (MOSI0/GPIO10), U1.11 (MOSI)
/RF_RESET: J4.29 (GCLK1/GPIO5), U1.14 (RESET)
/RF_SCK: J4.23 (SCLK0/GPIO11), U1.12 (SCK)
GND: ANTENNA.2 (Ext), C1.2, C2.2, C3.2, C4.2, GND.1, H1.1, H2.1, J4.6 (GND), J4.9 (GND), J4.14 (GND), J4.20 (GND), J4.25 (GND), J4.30 (GND), J4.34 (GND), J4.39 (GND), PWR.1 (K), U1.2 (GND), U1.16 (GND), U1.17 (GND)
unnamed: PWR.2 (A), R2.1
unnamed: 1A.2, J4.2 (5V), J4.4 (5V)
